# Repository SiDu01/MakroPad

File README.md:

# MakroPad

Selbstgebautes Makro- und Mediapad auf Basis eines ESP32-S3-DevKitC-1:
16 mechanische Tasten, 3 analoge Slider und ein 128×64-OLED, per USB oder
Bluetooth LE mit einer Windows-Companion-App verbunden.

> Taste oder Slider bedienen → am PC passiert zuverlässig etwas → das OLED
> bestätigt es kurz.

## Status

Version 0.5.0. Funktioniert auf der Hardware:

- 16 Tasten und 3 Slider mit Aktionen (Medien, System-/Programm-/Vordergrund-
  Lautstärke, Tastenkombinationen, Webseiten, Programme, Profile)
- OLED mit Uhr, Profil, laufendem Titel und kurzen Einblendungen
- Profile mit automatischem Wechsel nach Programm im Vordergrund
- Medientasten und Lautstärke auch ohne laufende App (USB-HID)
- Verbindung zur App auch per Bluetooth LE: einmal in den Windows-Einstellungen
  „MakroPad“ koppeln und den Code vom OLED eingeben. Ist USB verbunden, hat USB
  Vorrang. Strom kommt weiterhin über USB (kein Akku). Taste 12 halten und 11
  drücken schaltet manuell zwischen USB und Bluetooth um.
- Windows-App mit Pad-Editor, Live-Spiegel des Displays, Tray und Autostart

Plan und nächste Meilensteine: [docs/REWRITE_PLAN.md](docs/REWRITE_PLAN.md).
Der alte Stand (0.2.0) ist über das Git-Tag `legacy-v0.2.0` erreichbar.

## Aufbau

| Ordner | Inhalt |
| --- | --- |
| `firmware/` | PlatformIO-Projekt (Arduino-Framework) |
| `app/` | .NET-10-/Avalonia-App für Windows |
| `hardware/case/` | Parametrisches OpenSCAD-Gehäuse mit STL-Exporten ([Anleitung](hardware/case/README.md)) |
| `installer/` | Inno-Setup-Installer und Release-Skript |
| `docs/` | [Konfiguration](docs/CONFIG.md), [Protokoll v2](docs/PROTOCOL.md), [Hardware/Pinout](docs/HARDWARE.md), [Gestaltung](docs/UI_DESIGN.md) |

## Bauen und testen

```powershell
# Firmware (im Ordner firmware/)
pio run
pio run -t upload
pio test -e native

# App
dotnet build app\MakroPad.sln
dotnet test app\MakroPad.sln
dotnet run --project app\MakroPad.App
dotnet run --project app\MakroPad.App -- --simulator   # ohne Hardware, nur mit debugMode

# Release: Installer + Firmware-Image nach release/
.\installer\build-release.ps1
```

Voraussetzungen: PlatformIO Core, .NET SDK 10, für die nativen Firmware-Tests
ein Host-gcc (z. B. WinLibs), für den Installer Inno Setup 6.

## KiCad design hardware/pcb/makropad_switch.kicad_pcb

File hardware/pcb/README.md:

# MakroPad Switch-Platine

2-lagige Platine für die 16 MX-Switches, direkt eingelötet. Jede Taste hat eine eigene Leitung
zum Stecker J1, der zweite Pin liegt auf GND (Masseflächen oben und unten). Keine Matrix, keine
Dioden: passt ohne Firmware-Änderung zu `config::ButtonPins`.

Die Platine wird von [makropad_switch_pcb.py](makropad_switch_pcb.py) erzeugt, die Maße kommen aus
[../case/makropad_case.scad](../case/makropad_case.scad) (oben im Skript, bei Gehäuseänderungen mitziehen).

```powershell
& "D:\Program Files\KiCad\10.0\bin\python.exe" makropad_switch_pcb.py
$k = "D:\Program Files\KiCad\10.0\bin\kicad-cli.exe"
& $k pcb drc --severity-all makropad_switch.kicad_pcb
& $k pcb export gerbers --layers "F.Cu,B.Cu,F.Mask,B.Mask,F.SilkS,B.SilkS,Edge.Cuts" --subtract-soldermask --no-x2 -o export\gerber makropad_switch.kicad_pcb
& $k pcb export drill --format excellon --excellon-separate-th -o export\gerber\ makropad_switch.kicad_pcb
Compress-Archive -Force -Path export\gerber\* -DestinationPath export\makropad_switch_jlcpcb.zip
```

## Bestellen (JLCPCB)

`export/makropad_switch_jlcpcb.zip` hochladen. 2 Lagen, 1.6 mm, sonst Standard. Keine Bestückung nötig
(nur THT). Die Platine ist ca. 95 × 84 mm.

## Design Rules

Ausgelegt nach den [Würth Elektronik BASIC Design Rules](https://www.we-online.com/files/pdf1/basic-design-rules-0423-cbt-en.pdf)
v2.0 (04/2023), Kategorie STANDARD, Außenlagen bis 1 oz Startfolie. Die Werte stehen als
Board-Regeln in der Datei, der KiCad-DRC prüft sie:

| Regel | Würth | Platine |
| --- | --- | --- |
| Kupferabstand (1 oz Startfolie) | ≥ 180 µm | ≥ 0.2 mm (DRC) |
| Leiterbreite | ≥ 120 µm | 250 µm |
| Kupfer zur gefrästen Kante | ≥ 0.23 mm | ≥ 0.5 mm |
| Loch zu Loch (verschiedenes Potenzial) | ≥ 500 µm | ≥ 0.5 mm für alle Löcher |
| Restring PTH (0.6 mm Pad bei 0.25 mm Loch) | ≥ 0.175 mm | 0.35 mm |
| Lötstopp-Freistellung / Steg / Überdeckung | ≥ 50 / 70 / 50 µm | 50 / 70 / 50 µm |
| Teardrops an Pad-Anschlüssen | empfohlen | an allen 32 Anschlüssen |
| Bestückungsdruck: Schrifthöhe auf Lötstopp | ≥ 1.5 mm | 1.5 mm |
| Bestückungsdruck: Linienbreite | ≥ 150 µm | ≥ 150 µm |
| Bestückungsdruck zu Kupfer / NPTH-Kante | ≥ 300 µm | ≥ 300 µm zu Pads (Skript-Check) |
| Abstand zwischen Beschriftungen | ≥ 200 µm | ≥ 200 µm |

Den Abstand zwischen Bestückungsdruck und Kupfer prüft das Skript selbst, weil KiCad den Druck
nur gegen Lötstopp-Öffnungen prüft. Geprüft wird gegen freiliegendes Kupfer (Pads und NPTH).
Leiterbahnen und Masseflächen unter Lötstopp sind bedruckbar.

## Stecker J1 → ESP32-S3-DevKitC-1

2×9-Stiftleiste (2.54 mm), Kunststoff auf der **Unterseite**, Stifte zeigen nach unten.
Alternativ Kabel direkt einlöten. Die Unterseite ist mit den Tastennummern beschriftet:

| J1 | 1 | 2 | 3 | 4 | 5 | 6 | 7 | 8 | 9 | 10 | 11 | 12 | 13 | 14 | 15 | 16 | G |
| --- | --- | --- | --- | --- | --- | --- | --- | --- | --- | --- | --- | --- | --- | --- | --- | --- | --- |
| GPIO | 4 | 5 | 6 | 7 | 10 | 11 | 12 | 13 | 14 | 15 | 16 | 17 | 18 | 21 | 39 | 40 | GND |

Beide `G`-Pins sind GND, einer reicht.

## Einbau

1. Switches in die Switch-Platte klicken (3- oder 5-Pin, die Löcher passen für beide).
2. Platine von unten auf die Switch-Pins setzen, satt anliegend verlöten.
3. Stiftleiste von unten einsetzen und verlöten (oder Kabel).
4. Switch-Platte samt Platine wie im Gehäuse-README in den Deckel schrauben. Die hintere
   Laschen-Schraube bleibt hinter der Platinenkante erreichbar.

Die Aussparung rechts hinten ist der Durchgang für die OLED-Kabel. Die Lasche mit J1 sitzt rechts
neben dem ESP32 (dort ist unter der Platine ca. 19 mm Platz).

Platz geprüft (OpenSCAD, Platine + 1.8 mm Lötspitzen + Stiftleiste gegen Schale, Deckel,
Switch-Platte, OLED-Rahmen und ESP32 mit 3.3 mm Bauteilhöhe): keine Kollision, über dem ESP32
bleiben 0.5–1 mm. Lötspitzen nach dem Löten kurz abknipsen.

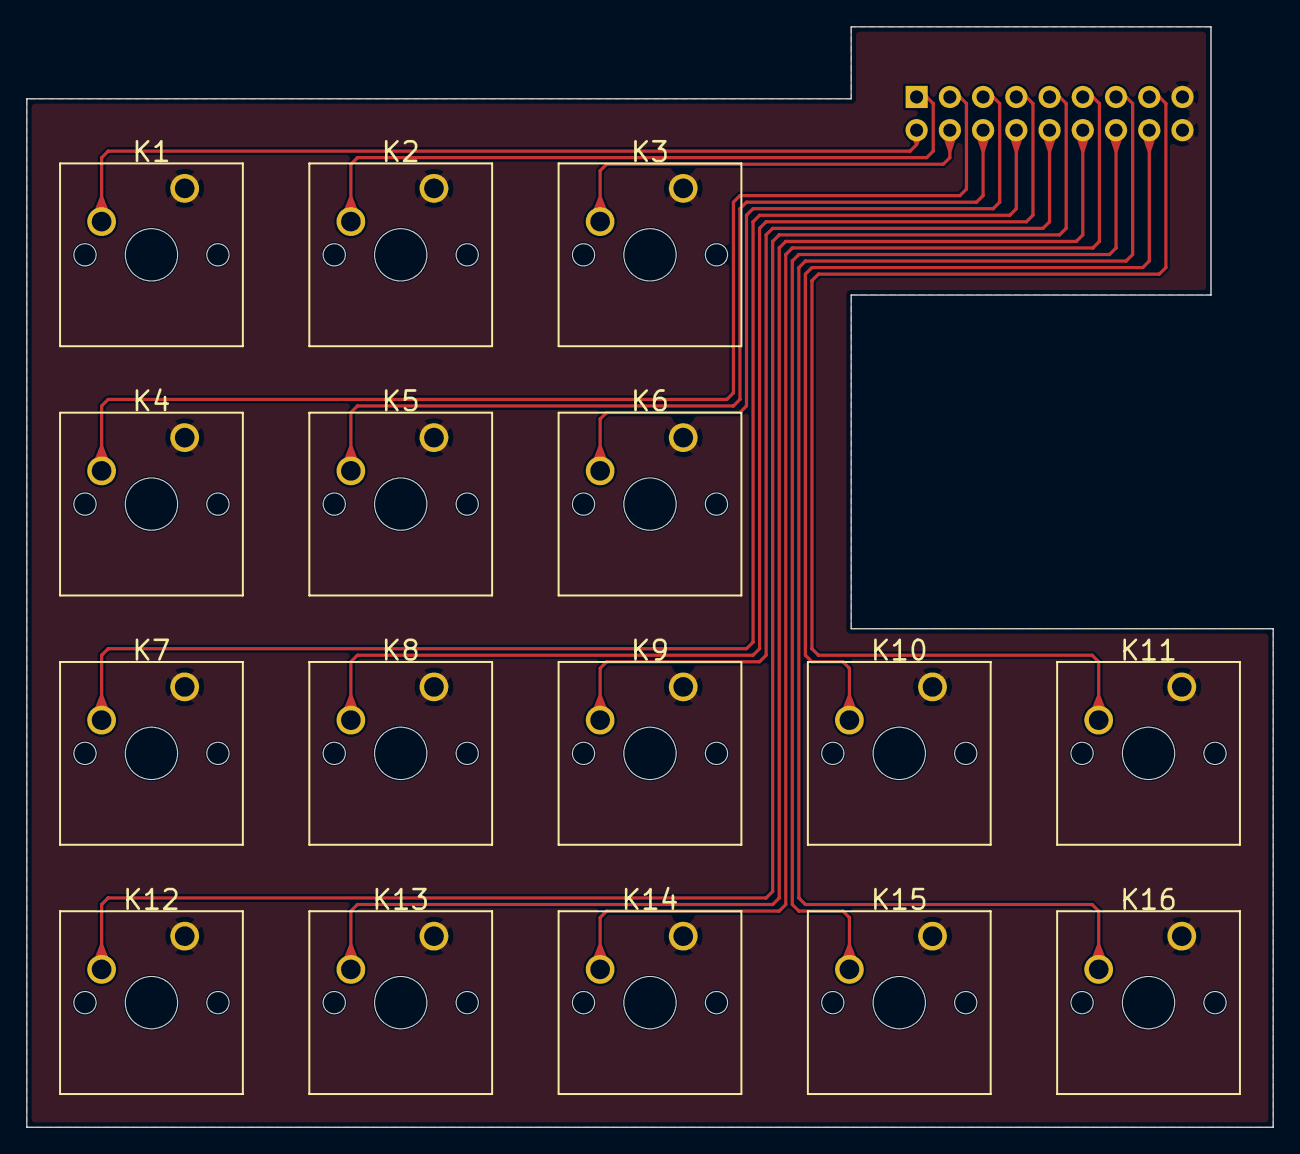
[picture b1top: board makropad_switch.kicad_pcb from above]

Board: 2 copper layers, 95.2 x 84.1 mm, 17 parts (1 on the bottom side), 17 nets.

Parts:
J1: to ESP32; PinHeader_2x09_P2.54mm_Vertical
K1, K2, K3, K4, K5, K6, K7, K8, K9, K10, K11, K12, K13, K14, K15, K16: MX; SW_Cherry_MX_1.00u_PCB

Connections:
GND: J1.17, J1.18, K1.1, K2.1, K3.1, K4.1, K5.1, K6.1, K7.1, K8.1, K9.1, K10.1, K11.1, K12.1, K13.1, K14.1, K15.1, K16.1
K1: J1.2, K1.2
K2: J1.1, K2.2
K3: J1.4, K3.2
K4: J1.3, K4.2
K5: J1.6, K5.2
K6: J1.5, K6.2
K7: J1.8, K7.2
K8: J1.7, K8.2
K9: J1.10, K9.2
K10: J1.16, K10.2
K11: J1.15, K11.2
K12: J1.9, K12.2
K13: J1.12, K13.2
K14: J1.11, K14.2
K15: J1.14, K15.2
K16: J1.13, K16.2

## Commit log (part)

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2026-05-14 Initial MakroPad project scaffold
2026-05-14 Add serial device connection
2026-05-14 Add tray background behavior
2026-05-14 Add configuration model
2026-05-14 Add initial action pipeline
2026-05-14 Fix serial robustness and add protocol tests
2026-05-14 Extract action pipeline and throttle sliders
2026-05-14 Implement Windows media play pause action
2026-05-14 Implement Windows system volume action
2026-05-14 Show profile bindings in app
2026-05-14 Update project documentation
2026-05-14 Refine main app layout
2026-05-29 Mirror firmware serial over UART
2026-05-29 Fix Windows media key input layout
2026-05-29 Add MakroPad auto connect
2026-05-29 Add basic profile binding editor
2026-05-29 Add common desktop actions
2026-05-29 Document config editor parameter hints
2026-05-29 Expand firmware input scanning
2026-05-29 Add OLED action result timeout
2026-06-01 Add serial heartbeat keepalive
2026-06-01 Improve config editor action hints
2026-06-01 Expand config editor controls
2026-06-01 Add config editor shortcut and app pickers
2026-06-01 Add OLED now playing display
2026-06-01 Restore media display after action timeout
2026-06-01 Redesign app shell with sidebar navigation
2026-06-01 Add application volume action
2026-06-01 Add configurable OLED default screen
2026-06-01 Expand OLED default screen placeholders
2026-06-01 Add OLED default screen preview
2026-06-01 Improve config editor and OLED layout
2026-06-02 Auto-refresh audio sessions in editor
2026-06-02 Add agent workflow guidance
2026-06-02 Add graphify project graph
2026-06-02 Update docs and handoff
2026-06-02 Split audio and OLED view model logic
2026-06-02 Extract now playing view model
2026-06-02 Extract device display sync service
2026-06-02 Add volume slider deadband
2026-06-02 Make volume slider deadband configurable
2026-06-02 Add OLED display slider triggers
2026-06-02 Rework settings navigation layout
2026-06-02 Make app screens stretch responsively
2026-06-02 Move settings pages into main navigation
2026-06-02 Add display trigger list editor
2026-06-02 Add display trigger test action
2026-06-02 Send matching display triggers in sequence
2026-06-02 Add display trigger ordering controls
2026-06-02 Add display trigger conditions and preview
2026-06-03 Make action result screens configurable
2026-06-03 Make media screens configurable
2026-06-03 Add connection status display triggers
2026-06-03 Polish display trigger event editor
2026-06-03 Complete display trigger workflow
2026-06-03 Add profile config service
2026-06-03 Add display trigger config migrator
2026-06-03 Add action feedback coordinator tests
2026-06-03 Add display triggers editor view model
2026-06-04 Split main window services
2026-06-04 Extract profile and display settings editors
2026-06-04 Extract app runtime loops
2026-06-04 Add OLED line scrolling
2026-06-04 Add OLED template text sizes
2026-06-04 Add OLED default text sizes
2026-06-04 Add OLED default HTML mode
2026-06-04 Add structured OLED layout mode
2026-06-04 Polish OLED layout mode
2026-06-04 Redesign display editor
2026-06-04 Harden app layout minimum sizes
2026-06-04 Fix compact display dropdown sizing
2026-06-04 Stabilize firmware slider readings
2026-06-04 Add firmware HID fallback mode
2026-06-04 Improve HID fallback diagnostics
2026-06-04 Throttle HID fallback volume nudges
